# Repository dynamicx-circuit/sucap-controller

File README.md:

# SucapController
## 现在的问题
需要移植到Kicad库

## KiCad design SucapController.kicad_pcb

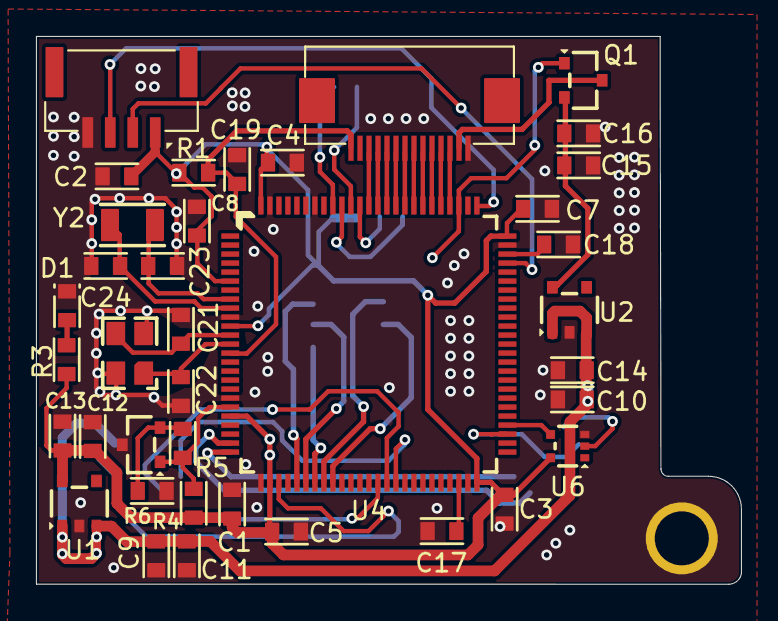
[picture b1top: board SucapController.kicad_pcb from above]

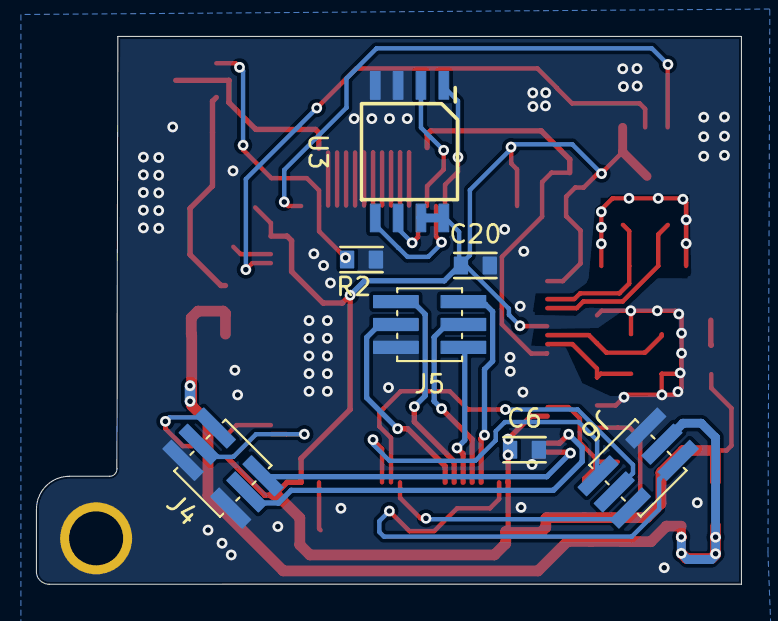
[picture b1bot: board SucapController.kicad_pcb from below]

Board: 2 copper layers, 39.2 x 30.4 mm, 46 parts (7 on the bottom side), 46 nets.

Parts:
 : TL431; SOT-23
 #2: GH1.25_H_4
 #3: Conn_01x14; FFC_14
 #4: Screw_Terminal_01x01; HOLE-04-03_1
 #5: 25M; SMD-3225_4
C1, C2, C3, C4, C5, C6, C7, C8, C11, C13, C14, C16, C19, C20: 100n; C0603(1608M)
C9, C10, C12, C15: 10u; C0603(1608M)
C17, C18: 2.2u; C0603(1608M)
C21, C22: 18p; C0603(1608M)
C23, C24: 10p; C0603(1608M)
D1: LED; LED0603(1608M)
J4, J5, J6: Conn_02x03_Counter_Clockwise; PINHEADER_02x03_1.27mm
Q1: SI2301; SOT-23
R1: 100n; R0603(1608M)
R2: 10K; R0603(1608M)
R3: 1k; R0603(1608M)
R4, R5: 10k; R0603(1608M)
R6: 50k; R0603(1608M)
U1: HX9193-33GB; SOT-23-5
U2: HX9193; SOT-23-5
U3: W25Q32JVSS; SOIC-5252_8
U4: STM32H750VBT6; QFP-1414_100
U6: 74LVC1G17; SOT-353
Y2: 32.768K; SMD-3215_2

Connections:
+3V3: #2.1, C1.2, C2.2, C3.2, C4.2, C5.2, C6.2, C7.2, C8.2, C12.2, C13.2, C20.2, R1.2, R3.2, R4.1, U1.5 (VOUT), U3.7 (~HOLD), U3.8 (VCC), U4.6 (Vbat), U4.11 (Vin), U4.21 (Vin_A), U4.27 (Vin), U4.50 (Vin), U4.75 (Vin), U4.100 (Vin), U6.5 (VCC)
+5V: C9.2, C10.2, C11.2, C14.2, J6.3, U1.1 (VIN), U1.3 (EN), U2.1 (VIN), U2.3 (EN)
/ADC_I1: J5.2, U4.30 (PA6)
/ADC_I2: J5.4, U4.31 (PA7)
/ADC_V1: J5.6, U4.32 (PC4)
/ADC_V2: J5.1, U4.33 (PC5)
/ADC_V3: J5.3, U4.34 (PB0)
/CAP_Boost: J6.4, U4.40 (PE10)
/CENTER: #3.11, U4.87 (PD6)
/CHG_EN: J6.6, U4.41 (PE11)
/CHG_ISET: J6.1, U4.28 (PA4)
/DOWN: #3.10, U4.86 (PD5)
/EN_MOS: J6.2, U4.39 (PE9)
/LCD_3V3: C15.2, C16.2, Q1.2 (Source), U2.5 (VOUT)
/LCD_CS: #3.7, U4.83 (PD2)
/LCD_DC: #3.6, U4.82 (PD1)
/LCD_EN: Q1.1 (Gate), R2.1, U4.78 (PC10)
/LCD_RST: #3.5, U4.81 (PD0)
/LCD_SCL: #3.3, U4.79 (PC11)
/LCD_SDA: #3.4, U4.80 (PC12)
/LEFT: #3.9, U4.85 (PD4)
/OSC32_IN: C23.2, U4.8 (PC14), Y2.2
/OSC32_OUT: C24.2, U4.9 (PC15), Y2.1
/OSC_IN: #5.3, C21.2, U4.12 (PH0)
/OSC_OUT: #5.1, C22.1, U4.13 (PH1)
/RESET: #3.14, C19.2, R1.1, U4.14 (nRST)
/RIGHT: #3.12, U4.88 (PD7)
/SPI1_CS: U3.1 (~CS), U4.92 (PB6)
/SPI1_MISO: U3.2 (DO), U4.90 (PB4)
/SPI1_MOSI: U3.5 (DI), U4.91 (PB5)
/SPI1_SCK: U3.6 (CLK), U4.89 (PB3)
/SWCLK: #2.3, U4.76 (PA14)
/SWDIO: #2.2, U4.72 (PA13)
/UART1_RX: U4.54 (PB15), U6.4 (Y)
/UART1_RX*: J4.1, U6.2 (A)
/UART1_TX: J4.3, U4.53 (PB14)
/UART2_RX: J4.2, U4.25 (PA3)
/UART2_TX: J4.4, U4.24 (PA2)
/UP: #3.8, U4.84 (PD3)
/VREF: .1 (K), R4.2, R5.2, U4.20 (Vref+)
GND: .3 (A), #2.4, #3.1, #4.1, #5.2, #5.4, C1.1, C2.1, C3.1, C4.1, C5.1, C6.1, C7.1, C8.1, C9.1, C10.1, C11.1, C12.1, C13.1, C14.1, C15.1, C16.1, C17.2, C18.2, C19.1, C20.1, C21.1, C22.2, C23.1, C24.1, D1.1 (Cathode), J4.5, J4.6, J5.5, J6.5, R2.2, R6.1, U1.2 (GND), U2.2 (GND), U3.3 (~WP), U3.4 (GND), U4.10 (GND), U4.19 (GND_A), U4.26 (GND), U4.49 (GND), U4.74 (GND), U4.94 (BOOT0), U4.99 (GND), U6.3 (GND)
unnamed: C17.1, U4.48 (Vcap_1)
unnamed: C18.1, U4.73 (Vcap_2)
unnamed: D1.2 (Anode), R3.1
unnamed: #3.2, Q1.3 (Drain)
unnamed: .2 (R), R5.1, R6.2

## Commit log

2022-07-11 Add .gitignore and READMD.md
2022-07-11 Update Sucap controller
2022-07-13 Do some change
2022-07-15 Turn the footprints into ours
2022-07-15 Turn REF3030 into TL431
2022-07-15 fix some error
2022-07-15 do some fix
2022-07-23 fix some error of TL431
